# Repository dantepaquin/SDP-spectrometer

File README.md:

# SDP-Spectrometer

This is the joint repository for the hardware and software for the UCSC EE SDP 2021 Spectrometer. 
The directory *kicad-libraries* contains all of the design files for the hardware, including the schematics, kicad projects, footprint & symbol libraries, and gerbers.
The directory *microcontroller-libraries* contains all of the software used by our spectrometer.

## Kicad Libraries
In our design, we used [KiCad v5.1.0](https://www.kicad.org/blog/2019/03/KiCad-5.1.0-Release/) to create libraries for footprints, symbols, schematics, and pcbs. Currently, the initial designs are in their first revision, and we have fabricated prototypes to be tested.

While our design uses five separate boards connected with wires, all designs are located within a single KiCad project, "main.pro."

### Overview of directories:
#### Adafruit-PowerBoost-1000C-master/
Our design uses an existing power delivery board, and this folder contains the physical design documents that we referenced and used in our own.

#### Backup/
An almost-empty folder used for managing local backups and versioining. Can be removed.

#### RN4678dev/
This contains a kicad project and its design files for a development board, opening the SMD footprint to machine headers. These are not necessary for the final design.

#### Renders/
This contains PDF views of the current PCBs, shown with a small selection of layers.

#### SC70-Dev/
This is a development board used for the SC70 footprint, allowing breadboard verification of our systems. This contains a kicad project with the scematic and PCB files.

#### Separate/
This directory contains subdirectories for each of the five PCBs of our design, which allowed us to manufacture individual boards rather than the full set. This also includes the gerbers used to manufacture the initial run of boards. 

#### Wiring Diagram/
This was a development project to identify and plan the necessary connections between the components of our design. It exists for reference, and has no physical form.

#### spectrometer_core.pretty/
This is the footprint library directory, implementing the physical dimensions and connections of each device used in our design.

#### fp-lib-table
This file tells KiCad how to associate the symbols in our schematic with the footprints in spectrometer_core.pretty.

#### main-cache.lib
This file keeps track of all of the symbols used in the schematic.

#### main.kicad_pcb
This is the main PCB file, which is used to design and lay out the footprints into their physical form.

#### main.pro
**This is the main project file of the spectrometer.** Opening this with kicad will give you access to design and change the footprints, symbols, schematics, and PCBs of the design.

#### main.sch
This is the main schematic file, used to establish connections between the components of the design.

#### spectrometer_core.bck
This is a local backup of the spectrometer_core.dcm file, and can be removed.

#### spectrometer_core.dcm
This keeps track of any documentation we added to the symbol library.

#### spectrometer_core.lib
This is our main symbol library, used to represent the components as used on our schematic.

#### sym-lib-table
This keeps track of the symbol libraries used in the main project.

## Microcontroller Libraries

Our project uses a [TeensyLC](https://www.pjrc.com/teensy/teensyLC.html) running [Arduino](https://www.arduino.cc/en/software), and was developed in the Arduino IDE. This directory contains the code we were able to complete, and verious sketches of test programs.

### Overview of directories:

#### Bluetooth/
This directory contains the currnent state of the bluetooth library implementation. The files include CircularBuffer.c/h, used for UART communication; RN4678.cpp/h, the main library file for the RN4678 bluetooth module; and RN4678_Command.h, a file containing all of the available bluetooth commands.

#### Examples/
This directory includes arduino sketches used to verify both the hardware and minor software usage in our design. These will allow basic back-and-forth, following PC -> USB -> Teesny -> UART -> RN4678 -> Bluetooth -> Phone

#### TeesnyMain/
This is the main directory of code running on the TeensyLC, TeensyMain.ino, and includes state machines and libraries used in our design.  

#### Adafruit_SSD1306.cpp/h
This is an open library by Adafruit designed for our OLED screen, based on the SSD1306 driver IC.

#### FiniteStateMachine.cpp/h
This is an old backup of the driving state machine of our microcontroller. The updated version is in TeensyMain/

#### LED.cpp/h
These files are basic LED drivers for arduino, and can be ignored.

#### RN4678_Command.h
This is a backup of the same file located in Bluetooth/. Both files include usage documentation inside

#### TeensyMain.ino
This is an old backup of the main arduino sketch within TeensyMain/, and can be ignored.

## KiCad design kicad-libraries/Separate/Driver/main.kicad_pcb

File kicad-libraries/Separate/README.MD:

# Individual EDA files

This folder contains all of the individual projects for each of the boards.

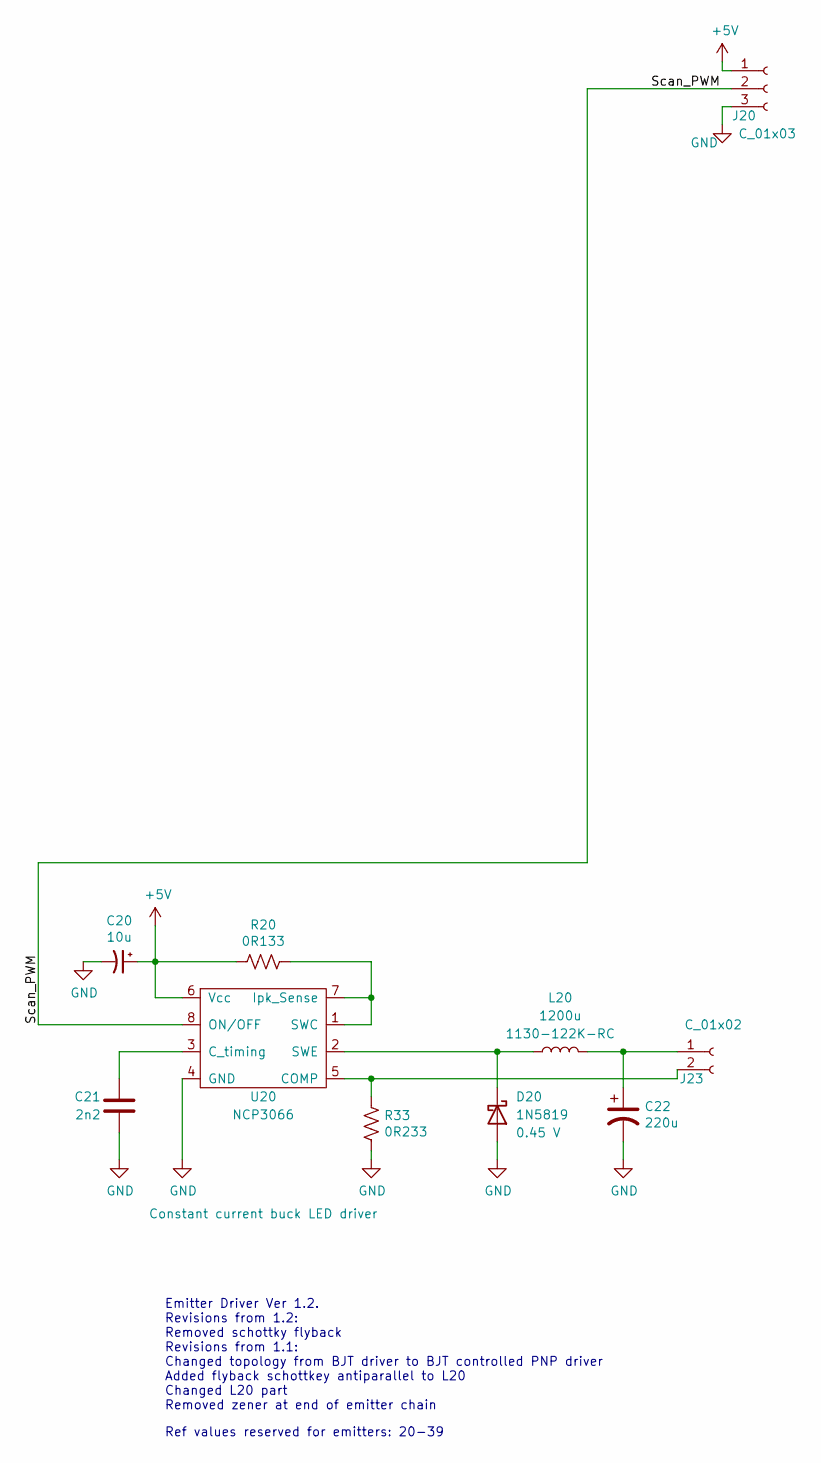
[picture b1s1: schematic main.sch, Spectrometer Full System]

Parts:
C20: 10u; CP_Elec_4x3
C21: 2n2; C_0603_1608Metric_Pad1.05x0.95mm_HandSolder
C22: 220u; CP_Elec_6.3x5.9
D20: 1N5819; D_DO-41_SOD81_P7.62mm_Horizontal
J20: C_01x03; 1x03_Vert_P2.00_Molex_Micro-Latch
J23: C_01x02; 1x02_Vert_P2.00_Molex_Micro-Latch
L20: 1200u; 1130-122K-RC
R20: 0R133; R_0805_2012Metric_Pad1.15x1.40mm_HandSolder
R33: 0R233; R_0805_2012Metric_Pad1.15x1.40mm_HandSolder
U20: NCP3066; SOIC-8

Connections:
+5V: C20.1, J20.1, R20.1, U20.6 (Vcc)
/Scan_PWM: J20.2, U20.8 (ON/OFF)
GND: C20.2, C21.2, C22.2, D20.2 (A), J20.3, R33.2, U20.4 (GND)
unnamed: C21.1, U20.3 (C_timing)
unnamed: C22.1, J23.1, L20.2
unnamed: D20.1 (K), L20.1, U20.2 (SWE)
unnamed: J23.2, R33.1, U20.5 (COMP)
unnamed: R20.2, U20.1 (SWC), U20.7 (Ipk_Sense)

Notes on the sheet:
Emitter Driver Ver 1.2. Revisions from 1.2: Removed schottky flyback Revisions from 1.1: Changed topology from BJT driver to BJT controlled PNP driver Added flyback schottkey antiparallel to L20 Changed L20 part Removed zener at end of emitter chain
Ref values reserved for emitters: 20-39

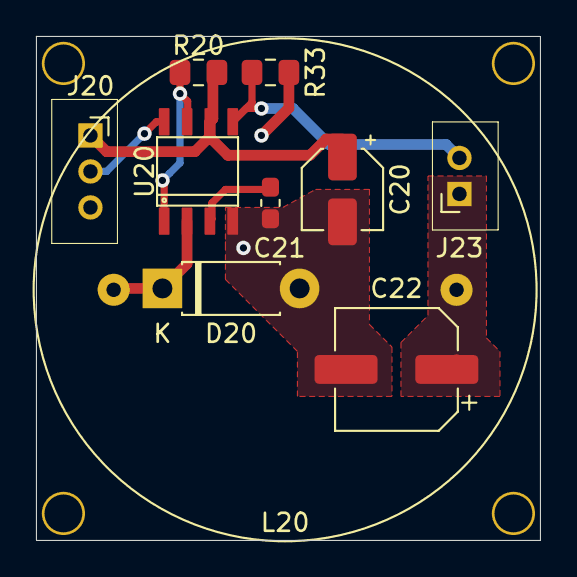
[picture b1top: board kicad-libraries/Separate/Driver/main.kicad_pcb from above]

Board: 2 copper layers, 28.0 x 28.0 mm, 10 parts (0 on the bottom side), 8 nets.

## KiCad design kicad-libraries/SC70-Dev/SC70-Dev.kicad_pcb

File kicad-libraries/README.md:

# Repository for KiCad Libraries and design

Individual design files (footprints & symbols) will go into part-specific subfolders in the "Separate" folder

KiCad organization basics:  
.LIB files store SCHEMATIC SYMBOLS  
.PRETTY folders store FOOTPRINT MODELS  
The two should be associated in their current form. 

Further work includes building basic building-block circuits so that integration is easier later on.

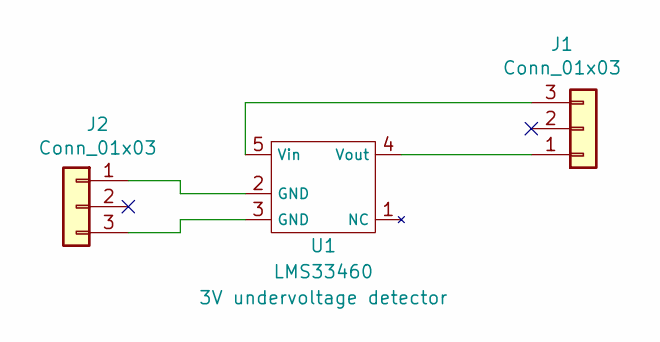
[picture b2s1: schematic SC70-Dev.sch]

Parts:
J1, J2: Conn_01x03; PinHeader_1x03_P2.54mm_Vertical
U1: LMS33460; SC70

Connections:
unnamed: J1.1, U1.4 (Vout)
unnamed: J1.3, U1.5 (Vin)
unnamed: J2.1, U1.2 (GND)
unnamed: J2.3, U1.3 (GND)

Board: 2 copper layers, 3 parts (0 on the bottom side), 4 nets, no tracks yet.

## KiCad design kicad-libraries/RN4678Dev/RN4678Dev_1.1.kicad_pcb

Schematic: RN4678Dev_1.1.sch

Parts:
C1, C2: C; C_0603_1608Metric
D1: LED; LED_0603_1608Metric
J1, J2: Conn_01x11_Male; PinHeader_1x11_P2.54mm_Vertical
JP1, JP2, JP3: J3; PinHeader_1x03_P2.54mm_Vertical
M1: RN4678
R1: R; R_0603_1608Metric

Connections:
+BATT: C1.1, J1.1, JP1.3, JP2.3, JP3.3, M1.4 (BAT_IN)
/04: J1.5, M1.11 (P0_4)
/05: J1.9, M1.16 (P0_5)
/12: J1.7, M1.13 (P1_2)
/13: J1.8, M1.14 (P1_3)
/15: J1.6, M1.12 (P1_5)
/31: J2.5, M1.24 (P3_1)
/32: J2.6, M1.25 (P3_2)
/33: J2.7, M1.26 (P3_3)
/34: J2.8, M1.27 (P3_4)
/36: J2.9, M1.28 (P3_6)
/37: J2.10, M1.29 (P3_7)
/CTS: J2.1, M1.15 (P1_7/CTS)
/LDO33: C2.1, M1.6 (LDO33_O), M1.7 (VDD_IO), R1.2
/RST_N: J1.10, M1.21 (RST_N)
/RTS: J2.2, M1.17 (P0_0/RTS)
/RXD: J2.3, M1.22 (RXD)
/SWBTN: J1.3, M1.5 (SW_BTN)
/TXD: J2.4, M1.23 (TXD)
/WAKEUP: J1.4, M1.9 (WAKEUP)
GND: C1.2, C2.2, J1.2, J1.11, J2.11, JP1.1, JP2.1, JP3.1, M1.1 (GND), M1.2 (GND), M1.3 (GND), M1.31 (GND), M1.32 (GND), M1.33 (GND)
unnamed 21: D1.1 (K), M1.30 (LED); also elsewhere on the board
unnamed 22: R1.1; also elsewhere on the board
unnamed: JP1.2, M1.18 (P2_0)
unnamed: JP2.2, M1.19 (P2_4)
unnamed: JP3.2, M1.20 (EAN)

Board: 2 copper layers, 10 parts (3 on the bottom side), 26 nets, no tracks yet.

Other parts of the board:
>|: LED; LED_0603_1608Metric

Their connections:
unnamed 21: >|.1; also elsewhere on the board
unnamed 22: >|.2; also elsewhere on the board

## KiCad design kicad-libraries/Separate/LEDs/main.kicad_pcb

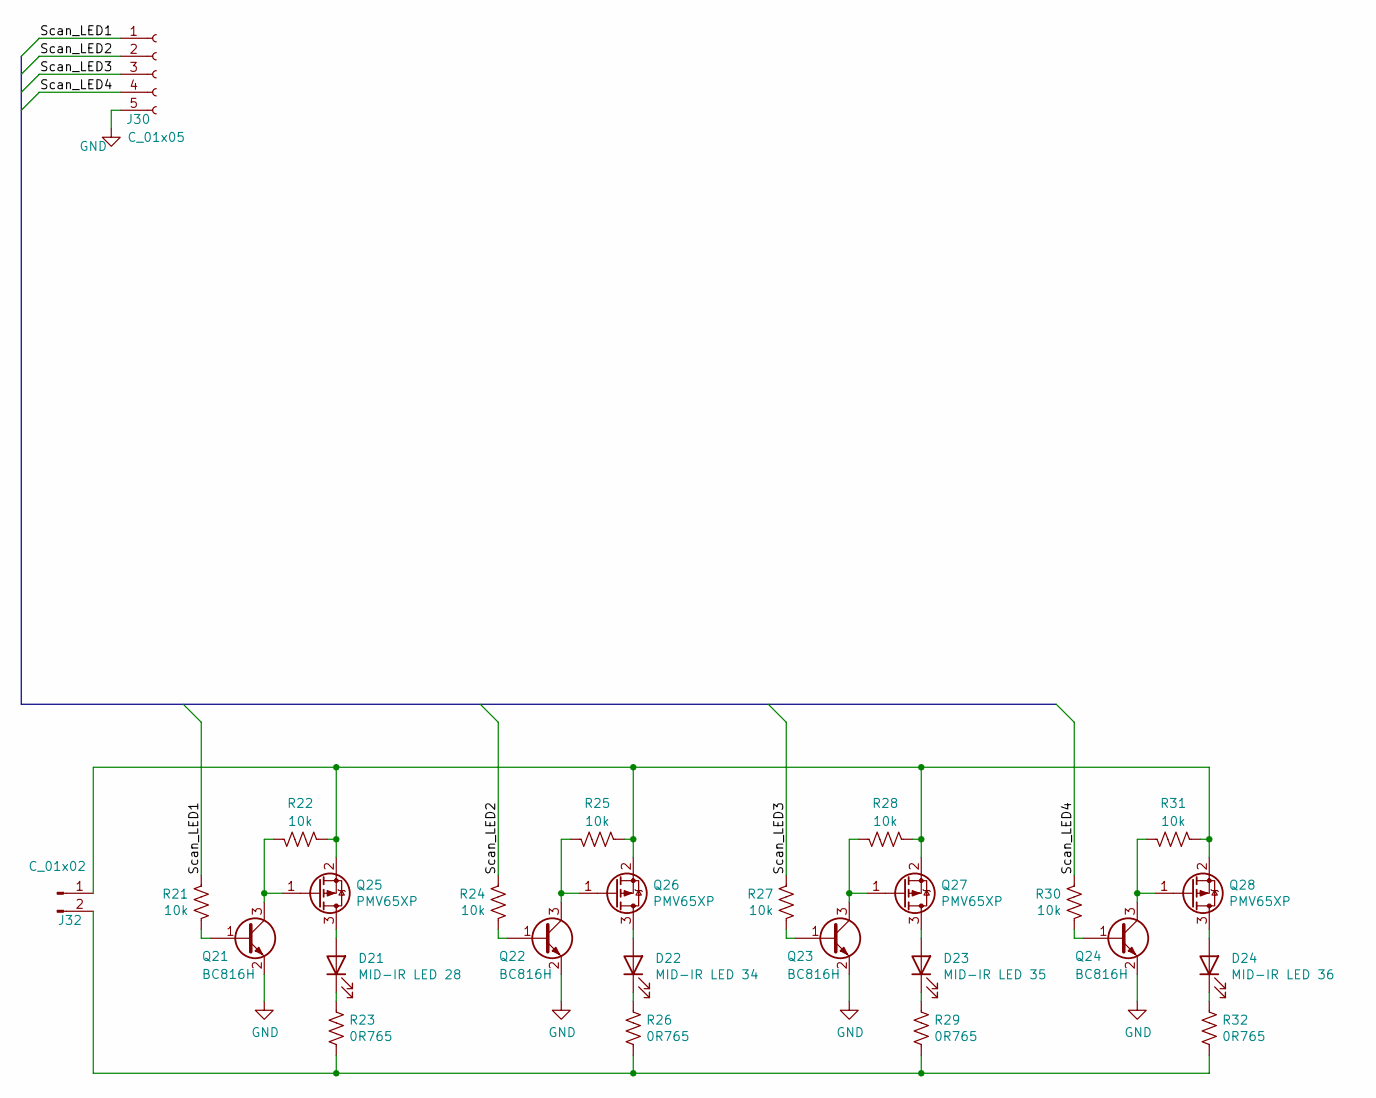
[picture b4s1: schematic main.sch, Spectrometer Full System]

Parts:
D21: MID-IR LED 28; TO-18R
D22: MID-IR LED 34; TO-18R
D23: MID-IR LED 35; TO-18R
D24: MID-IR LED 36; TO-18R
J30: C_01x05; 530480550
J32: C_01x02; 1x02_Horiz_P2.00_Molex_Micro-Latch
Q21, Q22, Q23, Q24: BC816H; SOT-23
Q25, Q26, Q27, Q28: PMV65XP; SOT-23
R21, R22, R24, R25, R27, R28, R30, R31: 10k; R_0603_1608Metric_Pad1.05x0.95mm_HandSolder
R23, R26, R29, R32: 0R765; R_0805_2012Metric_Pad1.15x1.40mm_HandSolder

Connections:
/Scan_LED1: J30.1, R21.1
/Scan_LED2: J30.2, R24.1
/Scan_LED3: J30.3, R27.1
/Scan_LED4: J30.4, R30.1
GND: J30.5, Q21.2 (E), Q22.2 (E), Q23.2 (E), Q24.2 (E)
unnamed: D21.1 (K), R23.1
unnamed: D21.2 (A), Q25.3 (D)
unnamed: D22.1 (K), R26.1
unnamed: D22.2 (A), Q26.3 (D)
unnamed: D23.1 (K), R29.1
unnamed: D23.2 (A), Q27.3 (D)
unnamed: D24.1 (K), R32.1
unnamed: D24.2 (A), Q28.3 (D)
unnamed: J32.1, Q25.2 (S), Q26.2 (S), Q27.2 (S), Q28.2 (S), R22.1, R25.1, R28.1, R31.1
unnamed: J32.2, R23.2, R26.2, R29.2, R32.2
unnamed: Q21.1 (B), R21.2
unnamed: Q21.3 (C), Q25.1 (G), R22.2
unnamed: Q22.1 (B), R24.2
unnamed: Q22.3 (C), Q26.1 (G), R25.2
unnamed: Q23.1 (B), R27.2
unnamed: Q23.3 (C), Q27.1 (G), R28.2
unnamed: Q24.1 (B), R30.2
unnamed: Q24.3 (C), Q28.1 (G), R31.2

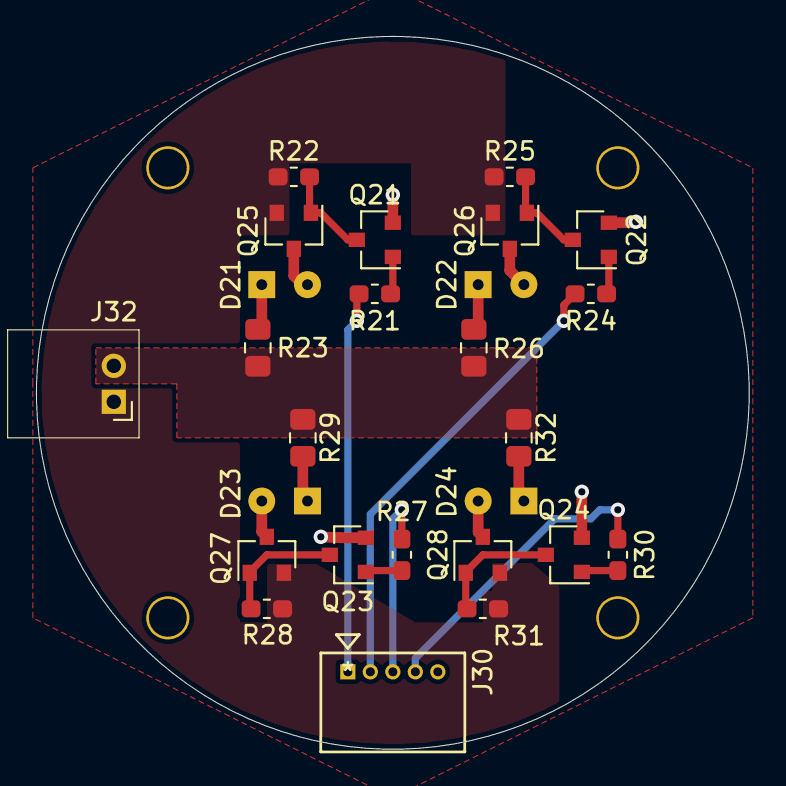
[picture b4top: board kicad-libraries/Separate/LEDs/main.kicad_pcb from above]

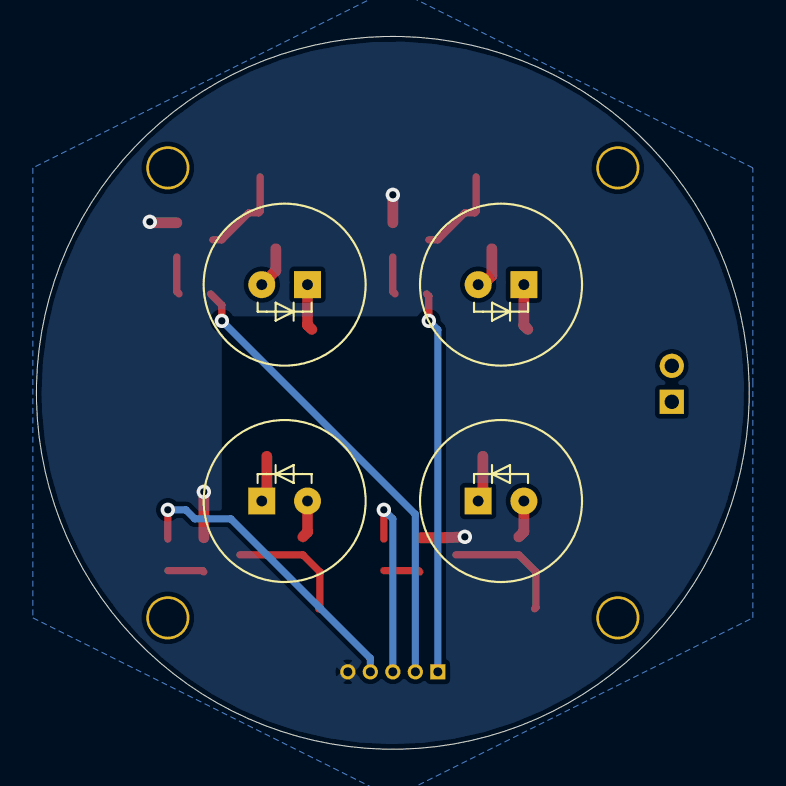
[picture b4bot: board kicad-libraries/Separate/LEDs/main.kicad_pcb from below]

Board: 2 copper layers, 39.6 x 39.6 mm, 26 parts (4 on the bottom side), 23 nets.

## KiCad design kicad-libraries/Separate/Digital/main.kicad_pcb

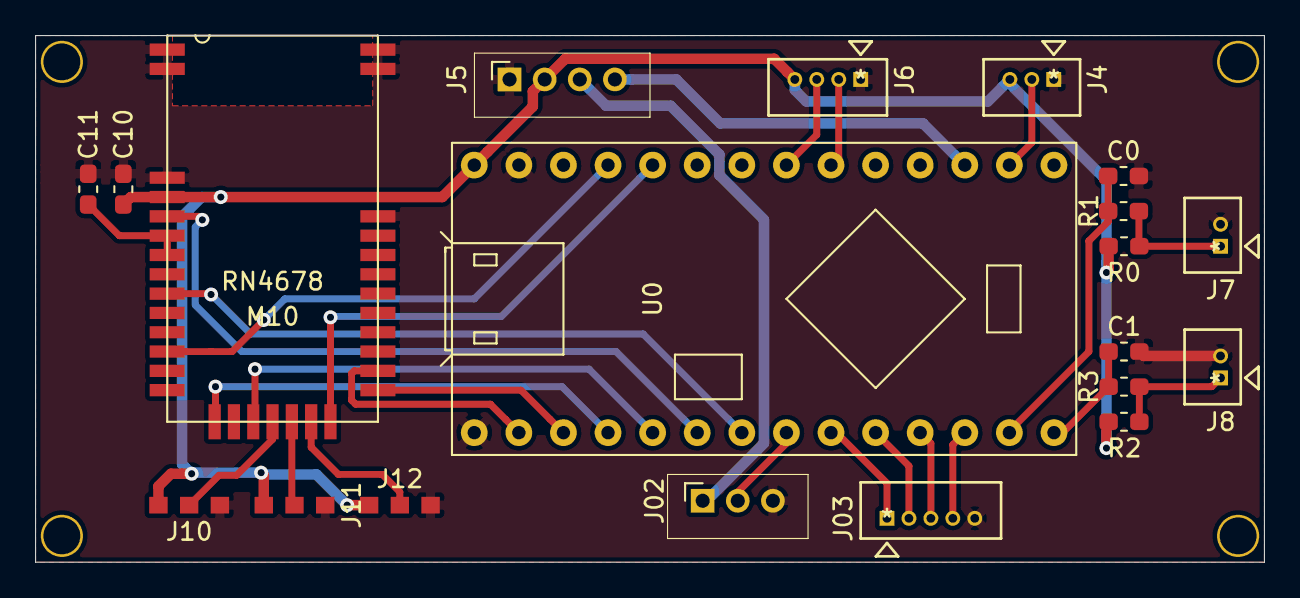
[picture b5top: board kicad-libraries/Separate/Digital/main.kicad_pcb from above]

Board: 2 copper layers, 70.0 x 30.0 mm, 20 parts (0 on the bottom side), 28 nets.

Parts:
C0, C1: 0.1u; C_0603_1608Metric_Pad1.05x0.95mm_HandSolder
C10: 10u; C_0603_1608Metric_Pad1.05x0.95mm_HandSolder
C11: 1u; C_0603_1608Metric_Pad1.05x0.95mm_HandSolder
J02: C_01x03; 1x03_Vert_P2.00_Molex_Micro-Latch
J03: C_01x05; 530470510
J4: C_01x03; 530470310
J5: C_01x04; 1x04_Vert_P2.00_Molex_Micro-Latch
J6: C_01x04; 530470410
J7, J8: C_01x02; 530470210
J10, J11, J12: Jmp3; Jumper3_0603
M10: RN4678
R0, R2: 100k; R_0603_1608Metric_Pad1.05x0.95mm_HandSolder
R1, R3: 1k; R_0603_1608Metric_Pad1.05x0.95mm_HandSolder
U0: TeensyLC_Inline

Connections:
+3V3: C10.1, J4.3, J5.2, J6.4, J10.1, J11.1, J12.1, M10.4, R0.1, R2.1, U0.VIN
+5V: J02.1, J5.3
+BATT: J5.4, U0.15
/BT_CTS: M10.15, U0.2
/BT_Power: M10.5, U0.4
/BT_RTS: M10.17, U0.3
/BT_Reset: M10.21, U0.22
/BT_Rx: M10.22, U0.1
/BT_Status: M10.12, U0.23
/BT_Tx: M10.23, U0.0
/BT_Wake: M10.9, U0.5
GND: C0.2, C1.2, C10.2, C11.1, J02.3, J03.5, J4.1, J5.1, J6.1, J7.2, J8.2, J10.2, J11.2, J12.2, M10.1, M10.2, M10.3, M10.31, M10.32, M10.33, U0.GND_1, U0.GND_3
unnamed: C0.1, R1.1, U0.11
unnamed: C1.1, R3.1, U0.12
unnamed: C11.2, M10.6, M10.7
unnamed: J02.2, U0.6
unnamed: J03.1, U0.7
unnamed: J03.2, U0.8
unnamed: J03.3, U0.9
unnamed: J03.4, U0.10
unnamed: J4.2, U0.14
unnamed: J6.2, U0.18
unnamed: J6.3, U0.19
unnamed: J7.1, R0.2, R1.2
unnamed: J8.1, R2.2, R3.2
unnamed: J10.3, M10.18
unnamed: J11.3, M10.19
unnamed: J12.3, M10.20

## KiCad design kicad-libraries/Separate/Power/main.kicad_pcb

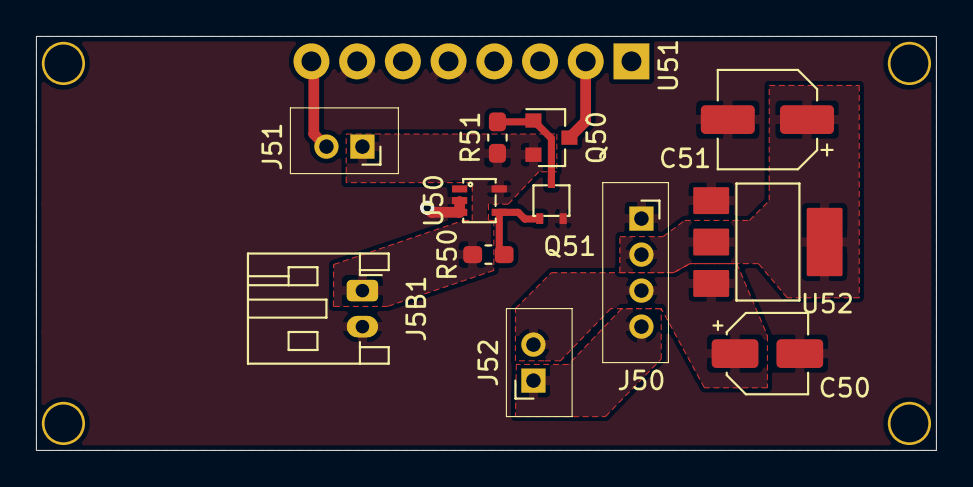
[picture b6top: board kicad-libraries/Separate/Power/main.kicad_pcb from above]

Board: 2 copper layers, 50.0 x 23.0 mm, 13 parts (0 on the bottom side), 9 nets.

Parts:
C50: 10u; CP_Elec_4x3
C51: 100u; CP_Elec_5x4.5
J5B1: C_01x02; JST_PH_S2B-PH-K_1x02_P2.00mm_Horizontal
J50: C_01x04; 1x04_Vert_P2.00_Molex_Micro-Latch
J51, J52: C_01x02; 1x02_Vert_P2.00_Molex_Micro-Latch
Q50: SSM3J372R; SOT-23
Q51: SSM3K127TU; UFM-3
R50: 470k; R_0603_1608Metric_Pad1.05x0.95mm_HandSolder
R51: 100k; R_0603_1608Metric_Pad1.05x0.95mm_HandSolder
U50: LMS33460; SC70
U51: PowerBoost1000C; Powerboost1000C
U52: LM1117; SOT-223

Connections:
GND: C50.2, C51.2, J5B1.2, J50.1, Q51.2, U50.2, U50.3, U51.5, U51.7, U52.1
unnamed: C50.1, J50.3, J52.2, U52.3
unnamed: C51.1, J50.2, U52.2
unnamed: J50.4, J52.1
unnamed: J5B1.1, J51.1, Q50.2, R50.1, R51.1, U50.5
unnamed: J51.2, U51.8
unnamed: Q50.1, Q51.3, R51.2
unnamed: Q50.3, U51.2
unnamed: Q51.1, R50.2, U50.4

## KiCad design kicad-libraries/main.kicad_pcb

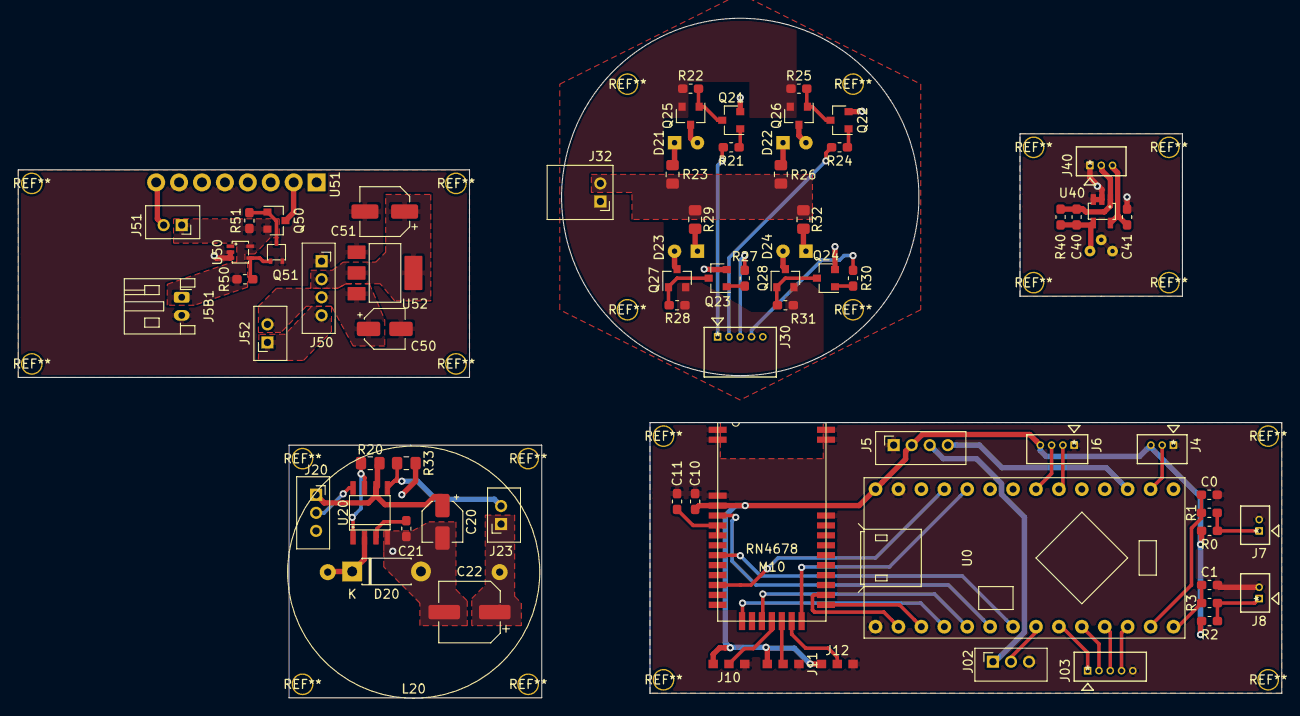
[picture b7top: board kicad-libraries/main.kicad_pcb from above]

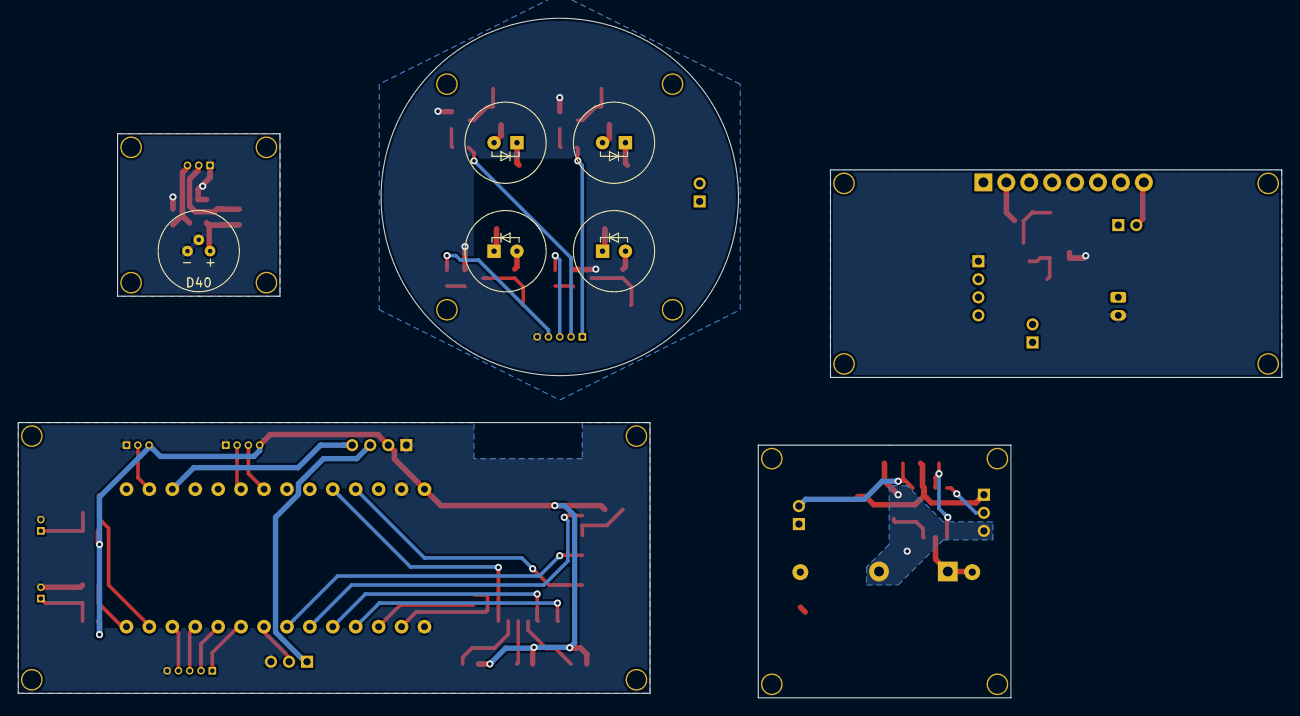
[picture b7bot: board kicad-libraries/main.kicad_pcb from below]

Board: 2 copper layers, 140.0 x 75.3 mm, 75 parts (5 on the bottom side), 66 nets.

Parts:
C0, C1, C41: 0.1u; C_0603_1608Metric_Pad1.05x0.95mm_HandSolder
C10: 10u; C_0603_1608Metric_Pad1.05x0.95mm_HandSolder
C11: 1u; C_0603_1608Metric_Pad1.05x0.95mm_HandSolder
C20, C50: 10u; CP_Elec_4x3
C21: 2n2; C_0603_1608Metric_Pad1.05x0.95mm_HandSolder
C22: 220u; CP_Elec_6.3x5.9
C40: 27n; C_0603_1608Metric_Pad1.05x0.95mm_HandSolder
C51: 100u; CP_Elec_5x4.5
D20: 1N5819; D_DO-41_SOD81_P7.62mm_Horizontal
D21: MID-IR LED 28; TO-18R
D22: MID-IR LED 34; TO-18R
D23: MID-IR LED 35; TO-18R
D24: MID-IR LED 36; TO-18R
D40: PD41-03; TO-18_WithReflector
J02, J20: C_01x03; 1x03_Vert_P2.00_Molex_Micro-Latch
J03: C_01x05; 530470510
J4, J40: C_01x03; 530470310
J5, J50: C_01x04; 1x04_Vert_P2.00_Molex_Micro-Latch
J5B1: C_01x02; JST_PH_S2B-PH-K_1x02_P2.00mm_Horizontal
J6: C_01x04; 530470410
J7, J8: C_01x02; 530470210
J10, J11, J12: Jmp3; Jumper3_0603
J23, J51, J52: C_01x02; 1x02_Vert_P2.00_Molex_Micro-Latch
J30: C_01x05; 530480550
J32: C_01x02; 1x02_Horiz_P2.00_Molex_Micro-Latch
L20: 1200u; 1130-122K-RC
M10: RN4678
Q21, Q22, Q23, Q24: BC816H; SOT-23
Q25, Q26, Q27, Q28: PMV65XP; SOT-23
Q50: SSM3J372R; SOT-23
Q51: SSM3K127TU; UFM-3
R0, R2, R51: 100k; R_0603_1608Metric_Pad1.05x0.95mm_HandSolder
R1, R3: 1k; R_0603_1608Metric_Pad1.05x0.95mm_HandSolder
R20: 0R133; R_0805_2012Metric_Pad1.15x1.40mm_HandSolder
R21, R22, R24, R25, R27, R28, R30, R31: 10k; R_0603_1608Metric_Pad1.05x0.95mm_HandSolder
R23, R26, R29, R32: 0R765; R_0805_2012Metric_Pad1.15x1.40mm_HandSolder
R33: 0R233; R_0805_2012Metric_Pad1.15x1.40mm_HandSolder
R40: 10k1; R_0603_1608Metric_Pad1.05x0.95mm_HandSolder
R50: 470k; R_0603_1608Metric_Pad1.05x0.95mm_HandSolder
U0: TeensyLC_Inline
U20: NCP3066; SOIC-8
U40: OPA990; SOT-23-5
U50: LMS33460; SC70
U51: PowerBoost1000C; Powerboost1000C
U52: LM1117; SOT-223

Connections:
+3V3: C10.1, C41.1, J4.3, J5.2, J6.4, J10.1, J11.1, J12.1, J40.3, M10.4, R0.1, R2.1, U0.VIN, U40.5
+5V: C20.1, J02.1, J5.3, J20.1, R20.1, U20.6
+BATT: J5.4, U0.15
/BT_CTS: M10.15, U0.2
/BT_Power: M10.5, U0.4
/BT_RTS: M10.17, U0.3
/BT_Reset: M10.21, U0.22
/BT_Rx: M10.22, U0.1
/BT_Status: M10.12, U0.23
/BT_Tx: M10.23, U0.0
/BT_Wake: M10.9, U0.5
/Scan_LED1: J30.1, R21.1
/Scan_LED2: J30.2, R24.1
/Scan_LED3: J30.3, R27.1
/Scan_LED4: J30.4, R30.1
/Scan_PWM: J20.2, U20.8
GND: C0.2, C1.2, C10.2, C11.1, C20.2, C21.2, C22.2, C41.2, C50.2, C51.2, D20.2, D40.1, D40.3, J02.3, J03.5, J4.1, J5.1, J5B1.2, J6.1, J7.2, J8.2, J10.2, J11.2, J12.2, J20.3, J30.5, J40.1, J50.1, M10.1, M10.2, M10.3, M10.31, M10.32, M10.33, Q21.2, Q22.2, Q23.2, Q24.2, Q51.2, R33.2, U0.GND_1, U0.GND_3, U20.4, U40.2, U40.3, U50.2, U50.3, U51.5, U51.7, U52.1
unnamed: C0.1, R1.1, U0.11
unnamed: C1.1, R3.1, U0.12
unnamed: C11.2, M10.6, M10.7
unnamed: C21.1, U20.3
unnamed: C22.1, J23.1, L20.2
unnamed: C40.1, J40.2, R40.2, U40.1
unnamed: C40.2, D40.2, R40.1, U40.4
unnamed: C50.1, J50.3, J52.2, U52.3
unnamed: C51.1, J50.2, U52.2
unnamed: D20.1, L20.1, U20.2
unnamed: D21.1, R23.1
unnamed: D21.2, Q25.3
unnamed: D22.1, R26.1
unnamed: D22.2, Q26.3
unnamed: D23.1, R29.1
unnamed: D23.2, Q27.3
unnamed: D24.1, R32.1
unnamed: D24.2, Q28.3
unnamed: J02.2, U0.6
unnamed: J03.1, U0.7
unnamed: J03.2, U0.8
unnamed: J03.3, U0.9
unnamed: J03.4, U0.10
unnamed: J4.2, U0.14
unnamed: J6.2, U0.18
unnamed: J6.3, U0.19
unnamed: J7.1, R0.2, R1.2
unnamed: J8.1, R2.2, R3.2
unnamed: J10.3, M10.18
unnamed: J11.3, M10.19
unnamed: J12.3, M10.20
unnamed: J23.2, R33.1, U20.5
unnamed: J32.1, Q25.2, Q26.2, Q27.2, Q28.2, R22.1, R25.1, R28.1, R31.1
unnamed: J32.2, R23.2, R26.2, R29.2, R32.2
unnamed: J50.4, J52.1
unnamed: J5B1.1, J51.1, Q50.2, R50.1, R51.1, U50.5
unnamed: J51.2, U51.8
unnamed: Q21.1, R21.2
unnamed: Q21.3, Q25.1, R22.2
unnamed: Q22.1, R24.2
unnamed: Q22.3, Q26.1, R25.2
unnamed: Q23.1, R27.2
unnamed: Q23.3, Q27.1, R28.2
unnamed: Q24.1, R30.2
unnamed: Q24.3, Q28.1, R31.2
unnamed: Q50.1, Q51.3, R51.2
unnamed: Q50.3, U51.2
unnamed: Q51.1, R50.2, U50.4
unnamed: R20.2, U20.1, U20.7

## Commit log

2021-07-30 added project files
2021-07-30 messed up smth
2021-07-30 added all project files
2021-08-14 Delete RN4678.h
    does not belong
2021-08-14 Update README.md
    Formatting
